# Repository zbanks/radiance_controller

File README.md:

Radiance Controller
===================

https://github.com/zbanks/radiance

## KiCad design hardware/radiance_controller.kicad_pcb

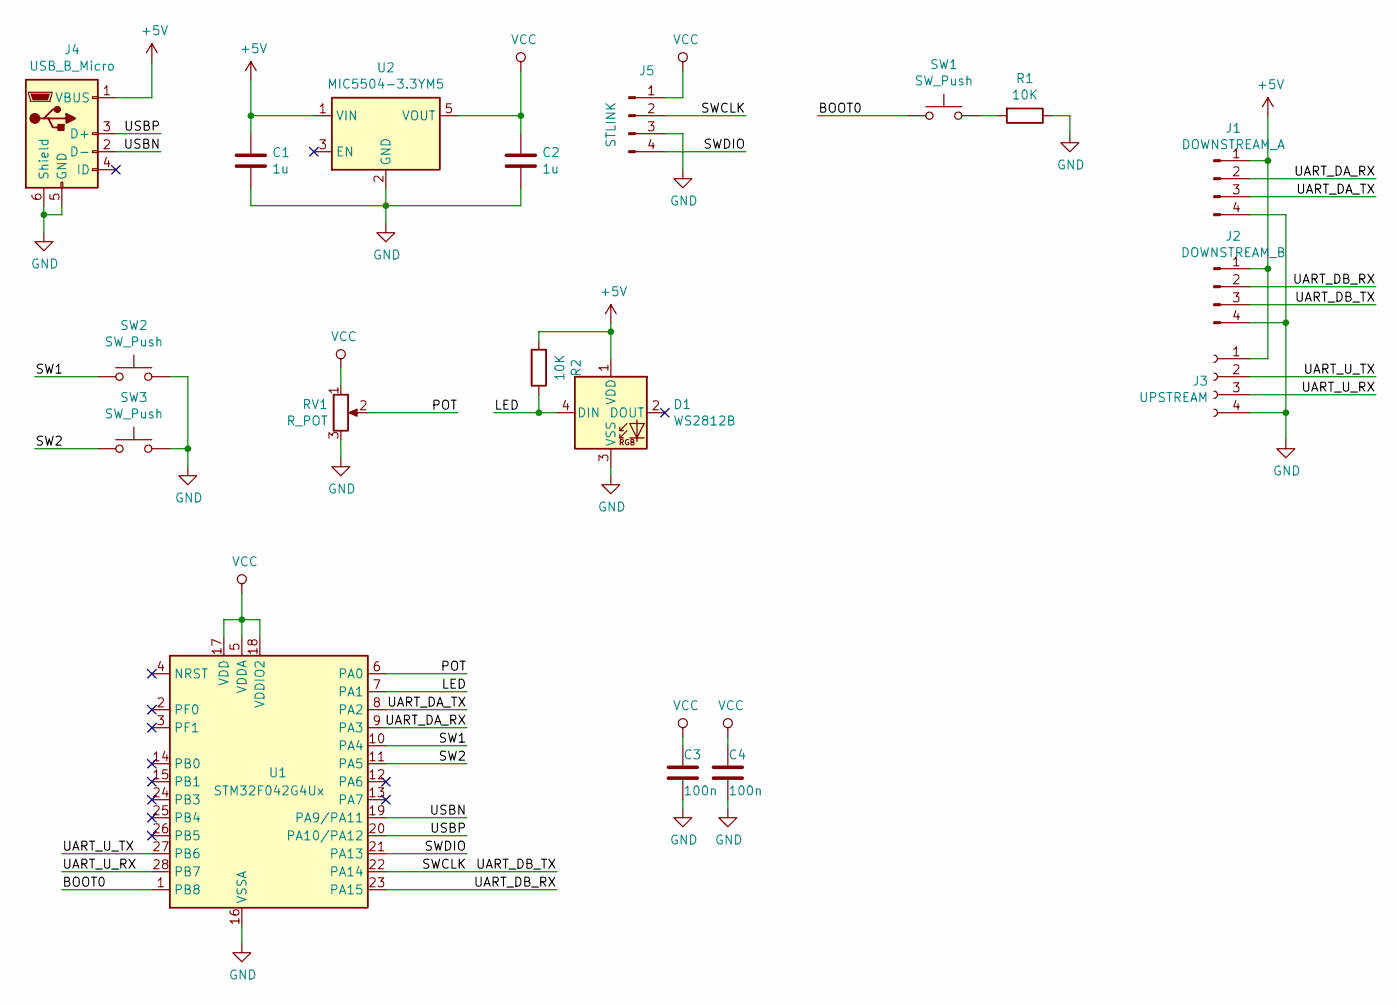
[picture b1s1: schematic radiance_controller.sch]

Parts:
C1, C2: 1u; C_0805_2012Metric_Pad1.15x1.40mm_HandSolder
C3, C4: 100n; C_0603_1608Metric_Pad1.05x0.95mm_HandSolder
D1: WS2812B; LED_WS2812B_PLCC4_5.0x5.0mm_P3.2mm
J1: DOWNSTREAM_A; PinHeader_1x04_P2.54mm_Horizontal
J2: DOWNSTREAM_B; PinHeader_1x04_P2.54mm_Horizontal
J3: UPSTREAM; PinSocket_1x04_P2.54mm_Horizontal
J4: USB_B_Micro; USB_Micro-B_Molex-105017-0001
J5: STLINK; PinHeader_1x04_P2.54mm_Vertical
R1, R2: 10K; R_0603_1608Metric_Pad1.05x0.95mm_HandSolder
RV1: R_POT; PTA2043
SW1, SW2, SW3: SW_Push; SW_SPST_FSMSM
U1: STM32F042G4Ux; QFN-28_4x4mm_P0.5mm
U2: MIC5504-3.3YM5; SOT-23-5_HandSoldering

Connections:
+5V: C1.1, D1.1 (VDD), J1.1, J2.1, J3.1, J4.1 (VBUS), R2.2, U2.1 (VIN)
/BOOT0: SW1.1, U1.1 (PB8)
/LED: D1.4 (DIN), R2.1, U1.7 (PA1)
/POT: RV1.2, U1.6 (PA0)
/SW1: SW2.1, U1.10 (PA4)
/SW2: SW3.1, U1.11 (PA5)
/SWCLK: J2.3, J5.2, U1.22 (PA14); also elsewhere on the board
/SWDIO: J5.4, U1.21 (PA13); also elsewhere on the board
/UART_DA_RX: J1.2, U1.9 (PA3)
/UART_DA_TX: J1.3, U1.8 (PA2)
/UART_DB_RX: J2.2, U1.23 (PA15)
/UART_U_RX: J3.3, U1.28 (PB7)
/UART_U_TX: J3.2, U1.27 (PB6)
/USBN: J4.2 (D-), U1.19 (PA9/PA11)
/USBP: J4.3 (D+), U1.20 (PA10/PA12)
GND: C1.2, C2.2, C3.2, C4.2, D1.3 (VSS), J1.4, J2.4, J3.4, J4.5 (GND), J4.6 (Shield), J5.3, R1.1, RV1.3, SW2.2, SW3.2, U1.16 (VSSA), U2.2 (GND); also elsewhere on the board
unnamed: R1.2, SW1.2
VCC: C2.1, C3.1, C4.1, J5.1, RV1.1, U1.5 (VDDA), U1.17 (VDD), U1.18 (VDDIO2), U2.5 (VOUT); also elsewhere on the board

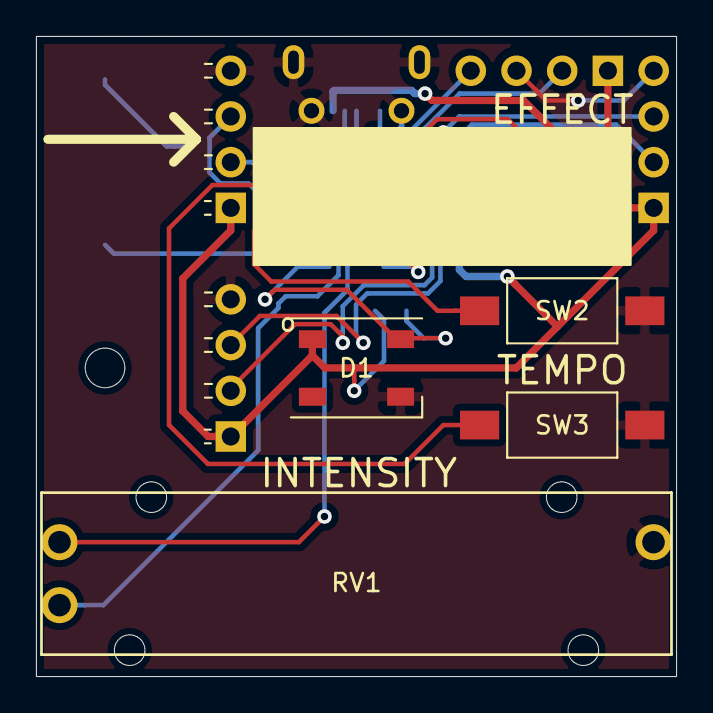
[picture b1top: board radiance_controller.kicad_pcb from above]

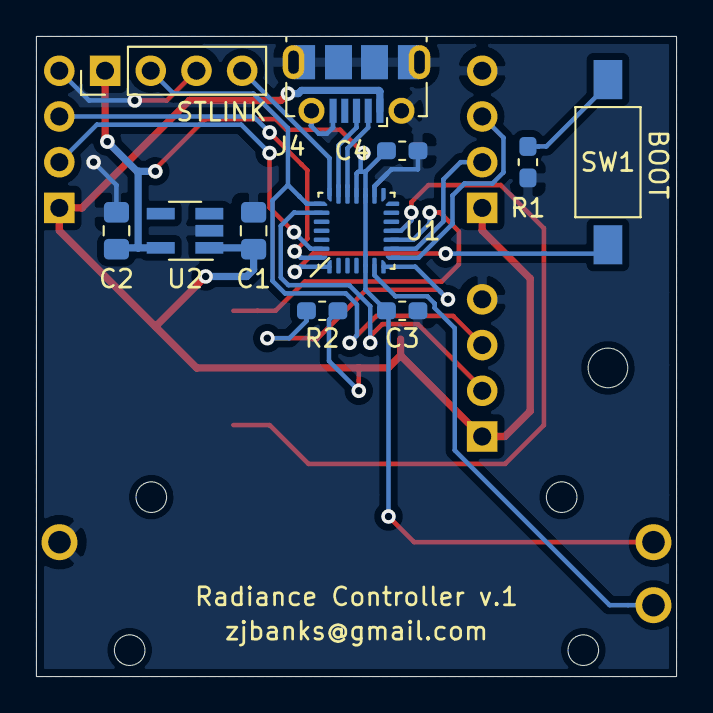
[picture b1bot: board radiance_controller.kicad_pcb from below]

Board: 2 copper layers, 35.6 x 35.6 mm, 18 parts (11 on the bottom side), 18 nets.

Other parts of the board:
STLINK: STLINK; PinHeader_1x04_P2.54mm_Vertical

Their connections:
/SWCLK: STLINK.2; also elsewhere on the board
/SWDIO: STLINK.4; also elsewhere on the board
GND: STLINK.3; also elsewhere on the board
VCC: STLINK.1; also elsewhere on the board

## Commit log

2019-07-20 Initial firmware commit
2019-07-20 USB ping pong
2019-07-28 LED sort of works
2019-07-28 Clean up some known garbage around LED
2019-07-28 Clean up LED stuff more now that it reliably works
2019-08-18 Duplex communication working
